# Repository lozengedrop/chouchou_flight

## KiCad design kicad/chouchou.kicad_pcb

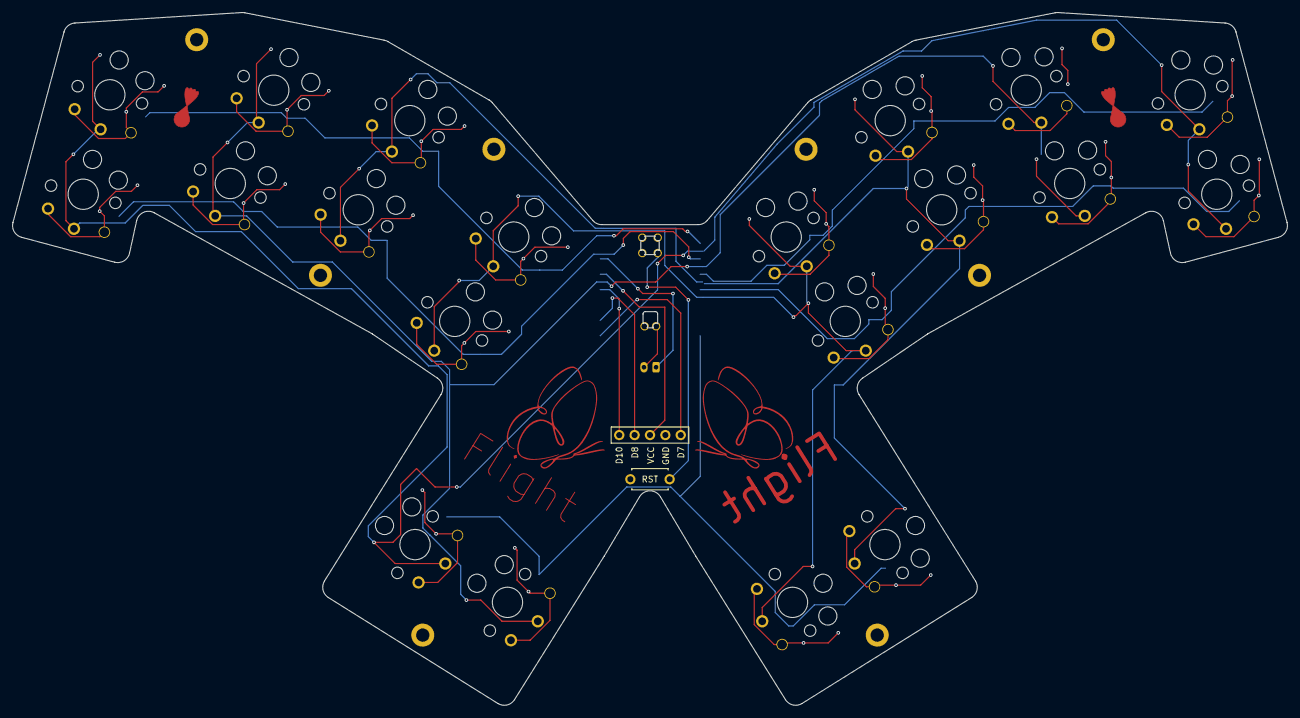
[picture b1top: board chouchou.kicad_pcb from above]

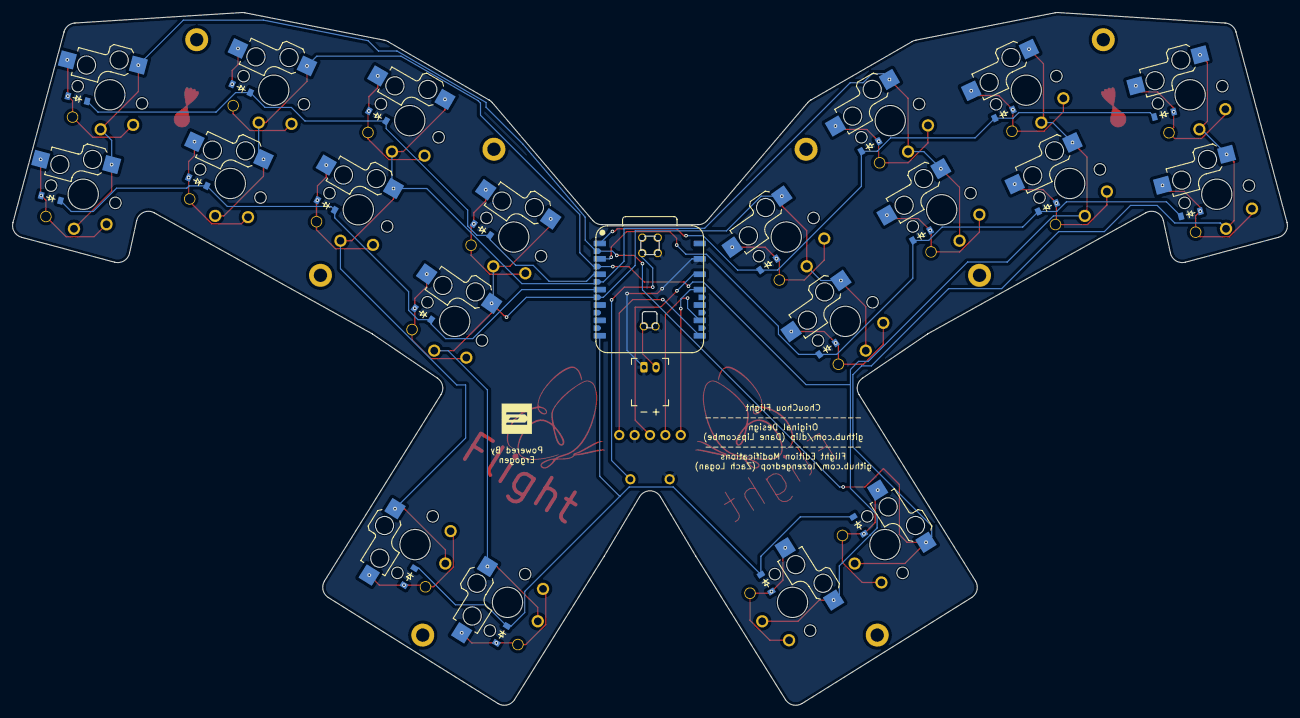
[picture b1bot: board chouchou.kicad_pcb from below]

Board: 2 copper layers, 210.5 x 114.4 mm, 52 parts (42 on the bottom side), 30 nets.

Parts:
D1, D2, D3, D4, D5, D6, D7, D8, D9, D10, D11, D12, D13, D14, D15, D16, D17, D18, D19, D20: diode_tht_sod123
DISP1: display_nice_view
H1, H2, H3, H4, H5, H6, H7, H8: mounting_hole_plated
JST1: battery_connector_jst_ph_2
LOGO1: utility_ergogen_logo
RST1: reset_switch_tht_top
S1, S2, S3, S4, S5, S6, S7, S8, S9, S10, S11, S12, S13, S14, S15, S16, S17, S18, S19, S20: switch_choc_v1_v2

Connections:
D0: D2.1, D4.1, D6.1, D8.1
D1: D1.1, D3.1, D5.1, D7.1
D2: D12.1, D14.1, D16.1, D18.1
D3: D11.1, D13.1, D15.1, D17.1
D6: D9.1, D10.1, D19.1, D20.1
D11: S1.1, S1.2, S2.1, S2.2, S9.1, S9.2, S10.1, S10.2, S17.1, S17.2
D12: S3.1, S3.2, S4.1, S4.2, S11.1, S11.2, S12.1, S12.2, S18.1, S18.2
D13: S5.1, S5.2, S6.1, S6.2, S13.1, S13.2, S14.1, S14.2, S19.1, S19.2
D14: S7.1, S7.2, S8.1, S8.2, S15.1, S15.2, S16.1, S16.2, S20.1, S20.2
GND: DISP1.4, JST1.1, RST1.2
index_bottom: D7.2, S7.1, S7.2
index_top: D8.2, S8.1, S8.2
inner_cluster: D9.2, S17.1, S17.2
middle_bottom: D5.2, S5.1, S5.2
middle_top: D6.2, S6.1, S6.2
mirror_index_bottom: D17.2, S15.1, S15.2
mirror_index_top: D18.2, S16.1, S16.2
mirror_inner_cluster: D19.2, S19.1, S19.2
mirror_middle_bottom: D15.2, S13.1, S13.2
mirror_middle_top: D16.2, S14.1, S14.2
mirror_outer_cluster: D20.2, S20.1, S20.2
mirror_pinky_bottom: D11.2, S9.1, S9.2
mirror_pinky_top: D12.2, S10.1, S10.2
mirror_ring_bottom: D13.2, S11.1, S11.2
mirror_ring_top: D14.2, S12.1, S12.2
outer_cluster: D10.2, S18.1, S18.2
pinky_bottom: D1.2, S1.1, S1.2
pinky_top: D2.2, S2.1, S2.2
ring_bottom: D3.2, S3.1, S3.2
ring_top: D4.2, S4.1, S4.2

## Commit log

2025-10-07 Update firmware backup
2026-06-11 Update config.yaml
    PCB wireless support: xiao ble plus mcu, nice!view display, & battery jst.
    ceoloide ergogen footprints.
    adjust mounting hole positions slightly to avoid hotswap conflicts.
2026-06-11 Space for battery
    Move jst and add pockets in case for battery and jst (also make case thicker to accomidate and reduce standoff height so pcb sits closer to base)
2026-06-12 move battery jst back to center to hide it under the display
2026-06-12 Add credits & keycap outlines
2026-06-13 Add reset switch to pcb & mcu pocket in case
2026-06-13 Update case.stl to support wireless (thicker base w/ pockets for battery & mcu)
2026-06-16 remove unused footprints & add footprint for xiao
2026-06-16 updated PDB (without images)
2026-06-16 Added Flight text to butterfly logos and added copper layer version
2026-06-16 Add graphics to the pcb
2026-06-16 Gerber update
